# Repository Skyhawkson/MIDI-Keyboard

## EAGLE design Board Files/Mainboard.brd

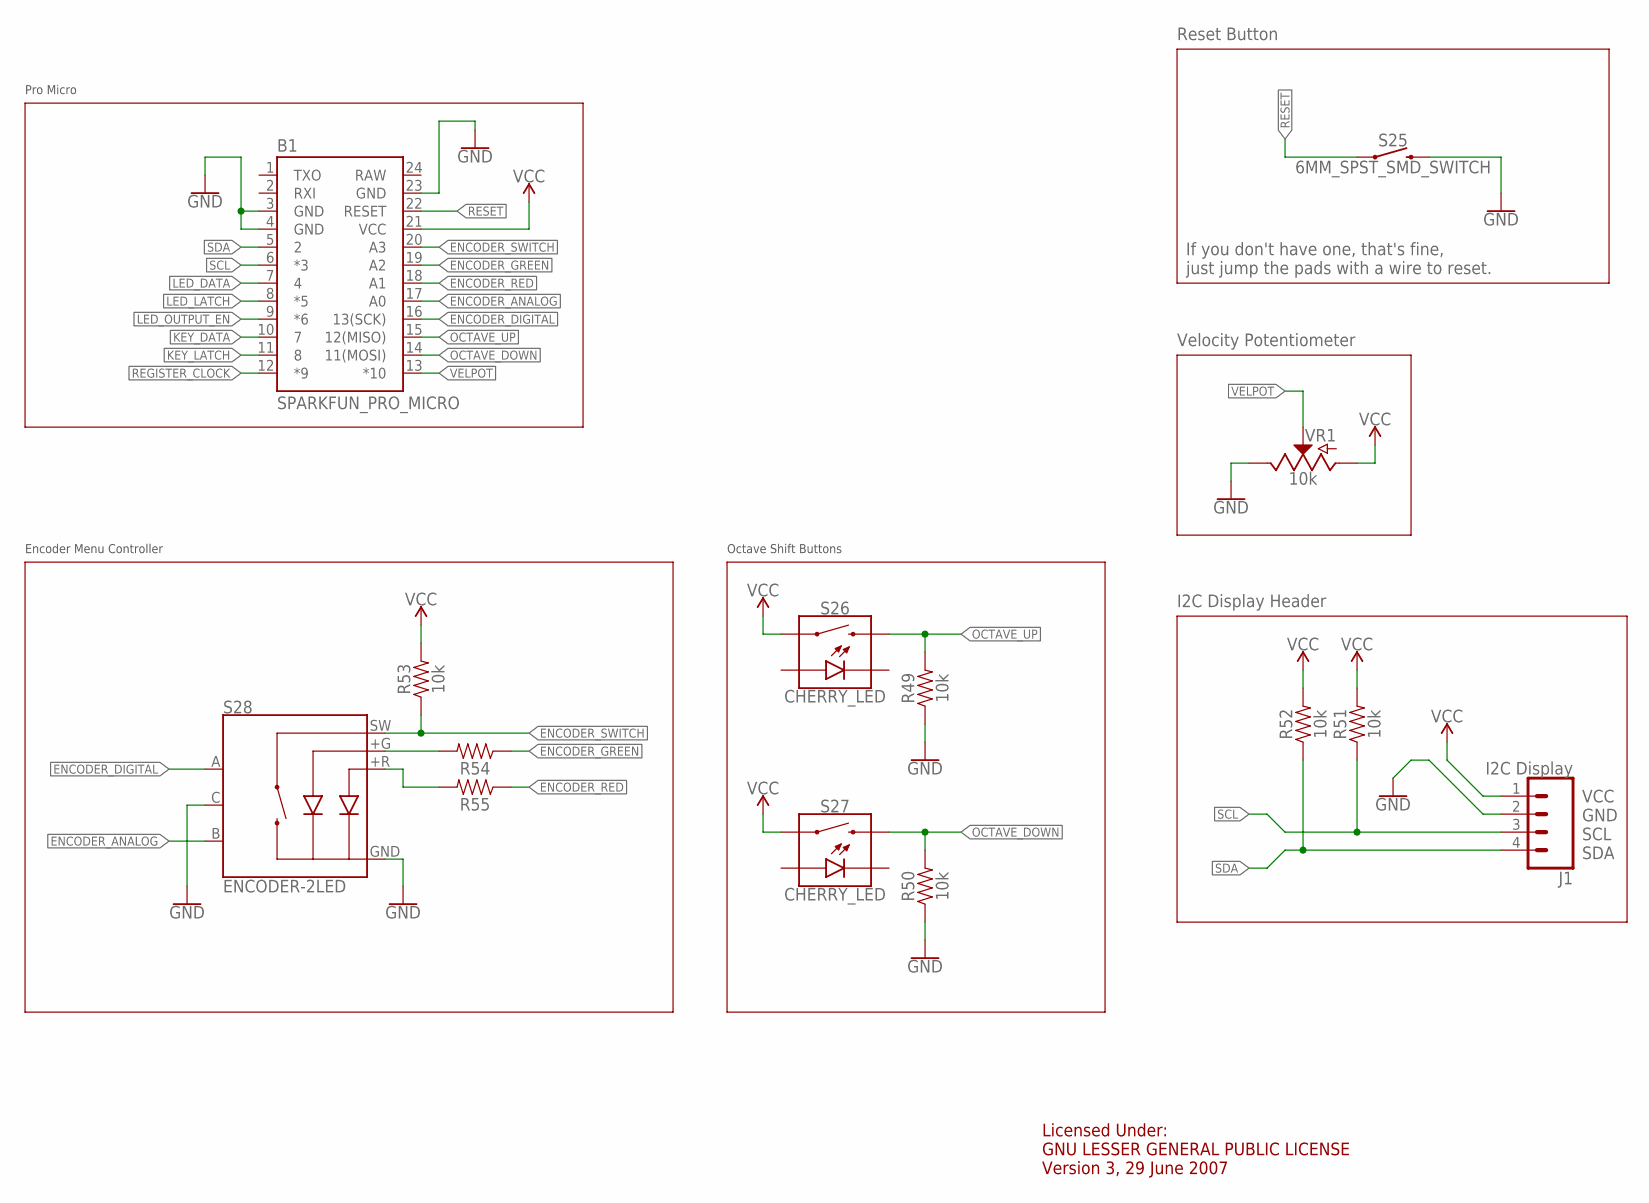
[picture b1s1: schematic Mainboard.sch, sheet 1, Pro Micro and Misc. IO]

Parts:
B1: SPARKFUN_PRO_MICRO
J1: I2C Display; 1X04
R49, R50, R51, R52, R53: 10k; AXIAL-0.3
R54, R55: AXIAL-0.3
S25: 6MM_SPST_SMD_SWITCH; TACTILE_SWITCH_SMD_6.0X3.5MM
S26, S27: CHERRY_LED; CHERRY-MX-LED
S28: ENCODER-2LED; ENCODER_LED_2
VR1: 10k; POT-PTH-ALPS

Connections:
ENCODER_ANALOG: B1.17 (A0), S28.B
ENCODER_DIGITAL: B1.16 (13(SCK)), S28.A
ENCODER_GREEN: B1.19 (A2), R54.P$1 (1)
ENCODER_RED: B1.18 (A1), R55.P$1 (1)
ENCODER_SWITCH: B1.20 (A3), R53.P$1 (1), S28.SW
GND: B1.3 (GND), B1.4 (GND), B1.23 (GND), J1.2, R49.P$1 (1), R50.P$1 (1), S25.2, S28.C, S28.GND (-), VR1.P$1 (E); also elsewhere on the board
KEY_DATA: B1.10 (7); also elsewhere on the board
KEY_LATCH: B1.11 (8); also elsewhere on the board
LED_DATA: B1.7 (4); also elsewhere on the board
LED_LATCH: B1.8 (*5); also elsewhere on the board
LED_OUTPUT_EN: B1.9 (*6); also elsewhere on the board
unnamed: R54.P$2 (2), S28.+G
unnamed: R55.P$2 (2), S28.+R
OCTAVE_DOWN: B1.14 (11(MOSI)), R50.P$2 (2), S27.S2 (2)
OCTAVE_UP: B1.15 (12(MISO)), R49.P$2 (2), S26.S2 (2)
RAW: B1.24 (RAW)
REGISTER_CLOCK: B1.12 (*9); also elsewhere on the board
RESET: B1.22 (RESET), S25.1
SCL: B1.6 (*3), J1.3, R51.P$1 (1)
SDA: B1.5 (2), J1.4, R52.P$1 (1)
VCC: B1.21 (VCC), J1.1, R51.P$2 (2), R52.P$2 (2), R53.P$2 (2), S26.S1 (1), S27.S1 (1), VR1.P$3 (A); also elsewhere on the board
VELPOT: B1.13 (*10), VR1.P$2 (S)

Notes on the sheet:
Reset Button
Velocity Potentiometer
VCC GND SCL SDA
I2C Display Header
If you don't have one, that's fine, just jump the pads with a wire to reset.
Licensed Under: GNU LESSER GENERAL PUBLIC LICENSE Version 3, 29 June 2007
Octave Shift Buttons
Encoder Menu Controller
Pro Micro

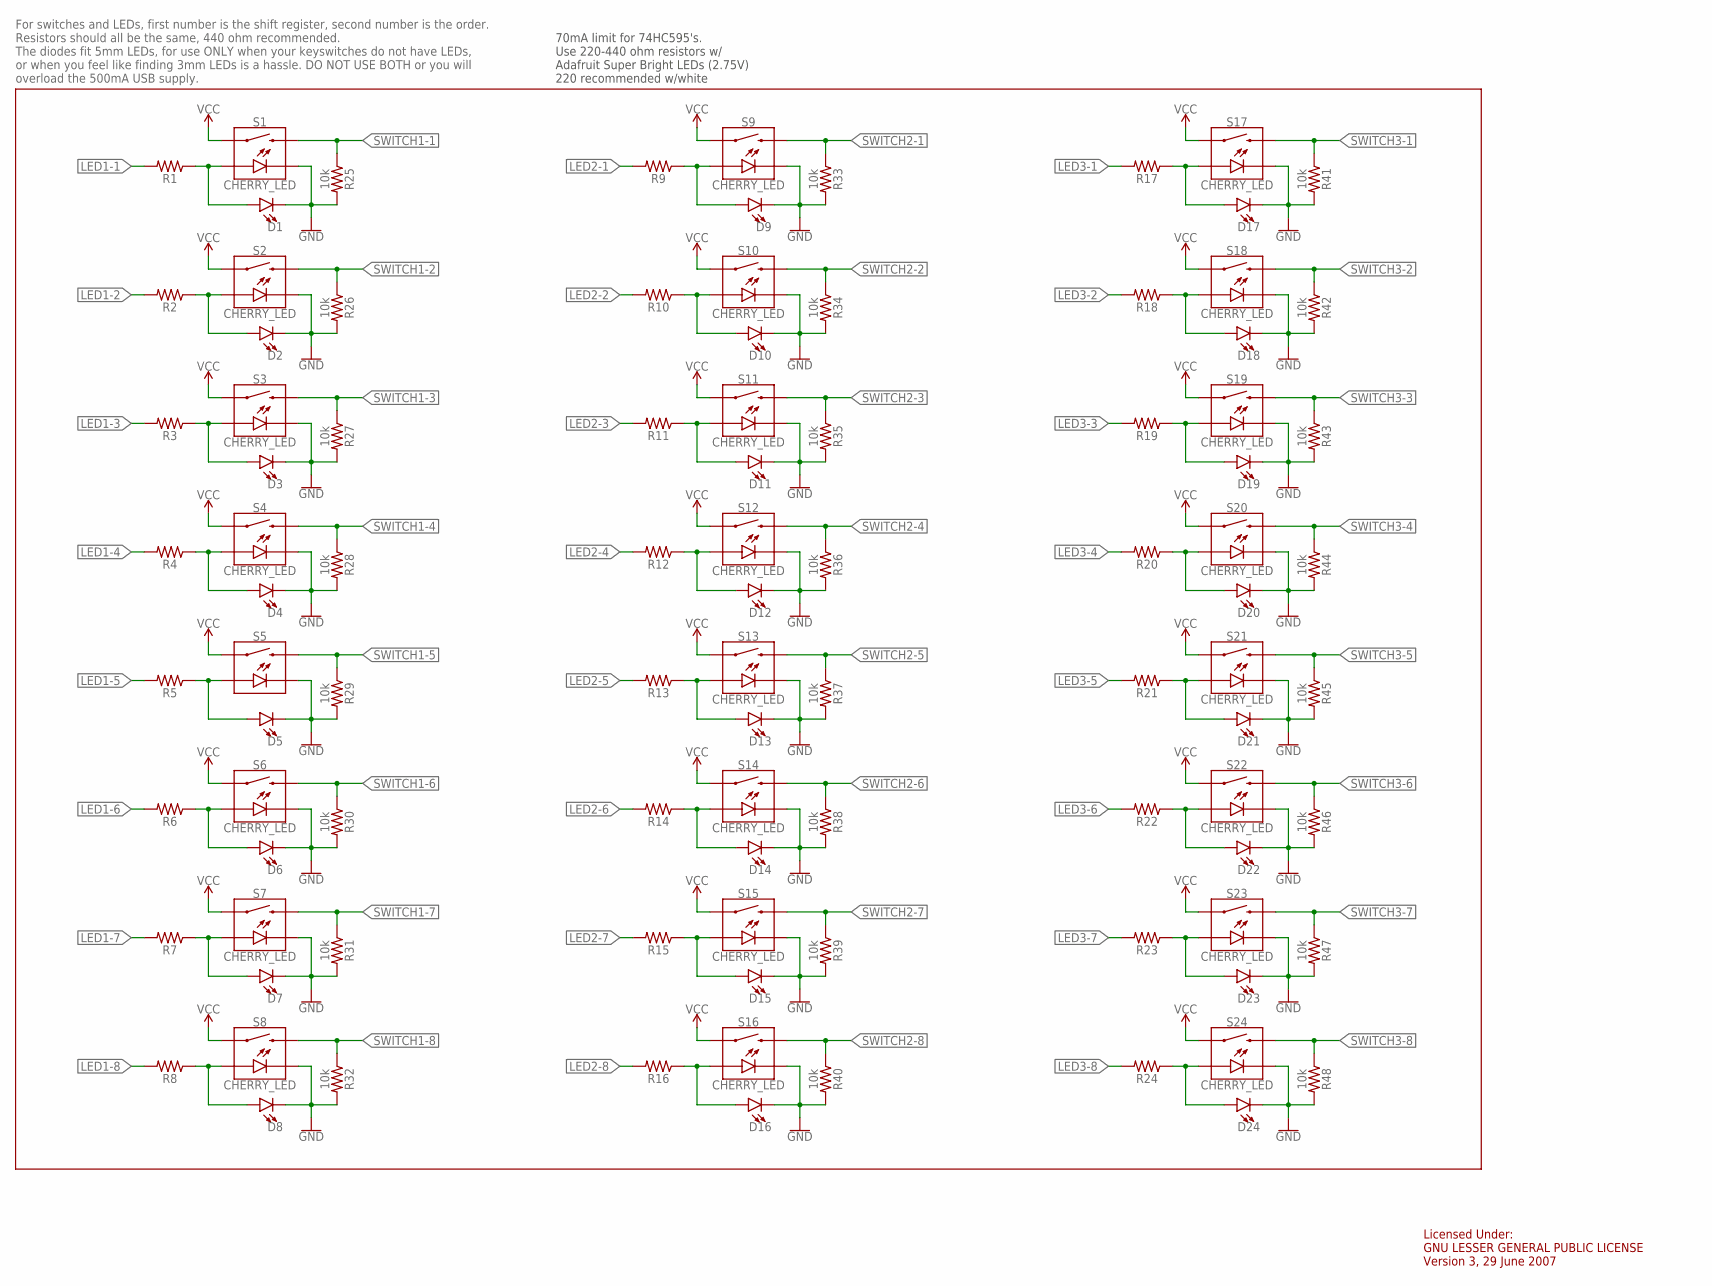
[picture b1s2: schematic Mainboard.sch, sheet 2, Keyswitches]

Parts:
D1, D2, D3, D4, D5, D6, D7, D8, D9, D10, D11, D12, D13, D14, D15, D16, D17, D18, D19, D20, D21, D22, D23, D24: LED5MM; LED_5MM
R1, R2, R3, R4, R5, R6, R7, R8, R9, R10, R11, R12, R13, R14, R15, R16, R17, R18, R19, R20, R21, R22, R23, R24: AXIAL-0.3
R25, R26, R27, R28, R29, R30, R31, R32, R33, R34, R35, R36, R37, R38, R39, R40, R41, R42, R43, R44, R45, R46, R47, R48: 10k; AXIAL-0.3
S1, S2, S3, S4, S6, S7, S8, S9, S10, S11, S12, S13, S14, S15, S16, S17, S18, S19, S20, S21, S22, S23, S24: CHERRY_LED; CHERRY-MX-LED
S5: MOMENTARY-SWITCH-SPST-LED-PTH-CHERRY; CHERRY-MX-LED

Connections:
GND: D1.K (C), D2.K (C), D3.K (C), D4.K (C), D5.K (C), D6.K (C), D7.K (C), D8.K (C), D9.K (C), D10.K (C), D11.K (C), D12.K (C), D13.K (C), D14.K (C), D15.K (C), D16.K (C), D17.K (C), D18.K (C), D19.K (C), D20.K (C), D21.K (C), D22.K (C), D23.K (C), D24.K (C), R25.P$2 (2), R26.P$2 (2), R27.P$2 (2), R28.P$2 (2), R29.P$2 (2), R30.P$2 (2), R31.P$2 (2), R32.P$2 (2), R33.P$2 (2), R34.P$2 (2), R35.P$2 (2), R36.P$2 (2), R37.P$2 (2), R38.P$2 (2), R39.P$2 (2), R40.P$2 (2), R41.P$2 (2), R42.P$2 (2), R43.P$2 (2), R44.P$2 (2), R45.P$2 (2), R46.P$2 (2), R47.P$2 (2), R48.P$2 (2), S1.K (C), S2.K (C), S3.K (C), S4.K (C), S5.K (C), S6.K (C), S7.K (C), S8.K (C), S9.K (C), S10.K (C), S11.K (C), S12.K (C), S13.K (C), S14.K (C), S15.K (C), S16.K (C), S17.K (C), S18.K (C), S19.K (C), S20.K (C), S21.K (C), S22.K (C), S23.K (C), S24.K (C); also elsewhere on the board
LED1-1: R1.P$2 (2); also elsewhere on the board
LED1-2: R2.P$2 (2); also elsewhere on the board
LED1-3: R3.P$2 (2); also elsewhere on the board
LED1-4: R4.P$2 (2); also elsewhere on the board
LED1-5: R5.P$2 (2); also elsewhere on the board
LED1-6: R6.P$2 (2); also elsewhere on the board
LED1-7: R7.P$2 (2); also elsewhere on the board
LED1-8: R8.P$2 (2); also elsewhere on the board
LED2-1: R9.P$2 (2); also elsewhere on the board
LED2-2: R10.P$2 (2); also elsewhere on the board
LED2-3: R11.P$2 (2); also elsewhere on the board
LED2-4: R12.P$2 (2); also elsewhere on the board
LED2-5: R13.P$2 (2); also elsewhere on the board
LED2-6: R14.P$2 (2); also elsewhere on the board
LED2-7: R15.P$2 (2); also elsewhere on the board
LED2-8: R16.P$2 (2); also elsewhere on the board
LED3-1: R17.P$2 (2); also elsewhere on the board
LED3-2: R18.P$2 (2); also elsewhere on the board
LED3-3: R19.P$2 (2); also elsewhere on the board
LED3-4: R20.P$2 (2); also elsewhere on the board
LED3-5: R21.P$2 (2); also elsewhere on the board
LED3-6: R22.P$2 (2); also elsewhere on the board
LED3-7: R23.P$2 (2); also elsewhere on the board
LED3-8: R24.P$2 (2); also elsewhere on the board
unnamed: D1.A, R1.P$1 (1), S1.A
unnamed: D2.A, R2.P$1 (1), S2.A
unnamed: D3.A, R3.P$1 (1), S3.A
unnamed: D4.A, R4.P$1 (1), S4.A
unnamed: D5.A, R5.P$1 (1), S5.A
unnamed: D6.A, R6.P$1 (1), S6.A
unnamed: D7.A, R7.P$1 (1), S7.A
unnamed: D8.A, R8.P$1 (1), S8.A
unnamed: D9.A, R9.P$1 (1), S9.A
unnamed: D10.A, R10.P$1 (1), S10.A
unnamed: D11.A, R11.P$1 (1), S11.A
unnamed: D12.A, R12.P$1 (1), S12.A
unnamed: D13.A, R13.P$1 (1), S13.A
unnamed: D14.A, R14.P$1 (1), S14.A
unnamed: D15.A, R15.P$1 (1), S15.A
unnamed: D16.A, R16.P$1 (1), S16.A
unnamed: D17.A, R17.P$1 (1), S17.A
unnamed: D18.A, R18.P$1 (1), S18.A
unnamed: D19.A, R19.P$1 (1), S19.A
unnamed: D20.A, R20.P$1 (1), S20.A
unnamed: D21.A, R21.P$1 (1), S21.A
unnamed: D22.A, R22.P$1 (1), S22.A
unnamed: D23.A, R23.P$1 (1), S23.A
unnamed: D24.A, R24.P$1 (1), S24.A
SWITCH1-1: R25.P$1 (1), S1.S2 (2); also elsewhere on the board
SWITCH1-2: R26.P$1 (1), S2.S2 (2); also elsewhere on the board
SWITCH1-3: R27.P$1 (1), S3.S2 (2); also elsewhere on the board
SWITCH1-4: R28.P$1 (1), S4.S2 (2); also elsewhere on the board
SWITCH1-5: R29.P$1 (1), S5.S2 (2); also elsewhere on the board
SWITCH1-6: R30.P$1 (1), S6.S2 (2); also elsewhere on the board
SWITCH1-7: R31.P$1 (1), S7.S2 (2); also elsewhere on the board
SWITCH1-8: R32.P$1 (1), S8.S2 (2); also elsewhere on the board
SWITCH2-1: R33.P$1 (1), S9.S2 (2); also elsewhere on the board
SWITCH2-2: R34.P$1 (1), S10.S2 (2); also elsewhere on the board
SWITCH2-3: R35.P$1 (1), S11.S2 (2); also elsewhere on the board
SWITCH2-4: R36.P$1 (1), S12.S2 (2); also elsewhere on the board
SWITCH2-5: R37.P$1 (1), S13.S2 (2); also elsewhere on the board
SWITCH2-6: R38.P$1 (1), S14.S2 (2); also elsewhere on the board
SWITCH2-7: R39.P$1 (1), S15.S2 (2); also elsewhere on the board
SWITCH2-8: R40.P$1 (1), S16.S2 (2); also elsewhere on the board
SWITCH3-1: R41.P$1 (1), S17.S2 (2); also elsewhere on the board
SWITCH3-2: R42.P$1 (1), S18.S2 (2); also elsewhere on the board
SWITCH3-3: R43.P$1 (1), S19.S2 (2); also elsewhere on the board
SWITCH3-4: R44.P$1 (1), S20.S2 (2); also elsewhere on the board
SWITCH3-5: R45.P$1 (1), S21.S2 (2); also elsewhere on the board
SWITCH3-6: R46.P$1 (1), S22.S2 (2); also elsewhere on the board
SWITCH3-7: R47.P$1 (1), S23.S2 (2); also elsewhere on the board
SWITCH3-8: R48.P$1 (1), S24.S2 (2); also elsewhere on the board
VCC: S1.S1 (1), S2.S1 (1), S3.S1 (1), S4.S1 (1), S5.S1 (1), S6.S1 (1), S7.S1 (1), S8.S1 (1), S9.S1 (1), S10.S1 (1), S11.S1 (1), S12.S1 (1), S13.S1 (1), S14.S1 (1), S15.S1 (1), S16.S1 (1), S17.S1 (1), S18.S1 (1), S19.S1 (1), S20.S1 (1), S21.S1 (1), S22.S1 (1), S23.S1 (1), S24.S1 (1); also elsewhere on the board

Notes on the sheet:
For switches and LEDs, first number is the shift register, second number is the order. Resistors should all be the same, 440 ohm recommended. The diodes fit 5mm LEDs, for use ONLY when your keyswitches do not have LEDs, or when you feel like finding 3mm LEDs is a hassle. DO NOT USE BOTH or you will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
70mA limit for 74HC595's. Use 220-440 ohm resistors w/ Adafruit Super Bright LEDs (2.75V) 220 recommended w/white
Licensed Under: GNU LESSER GENERAL PUBLIC LICENSE Version 3, 29 June 2007

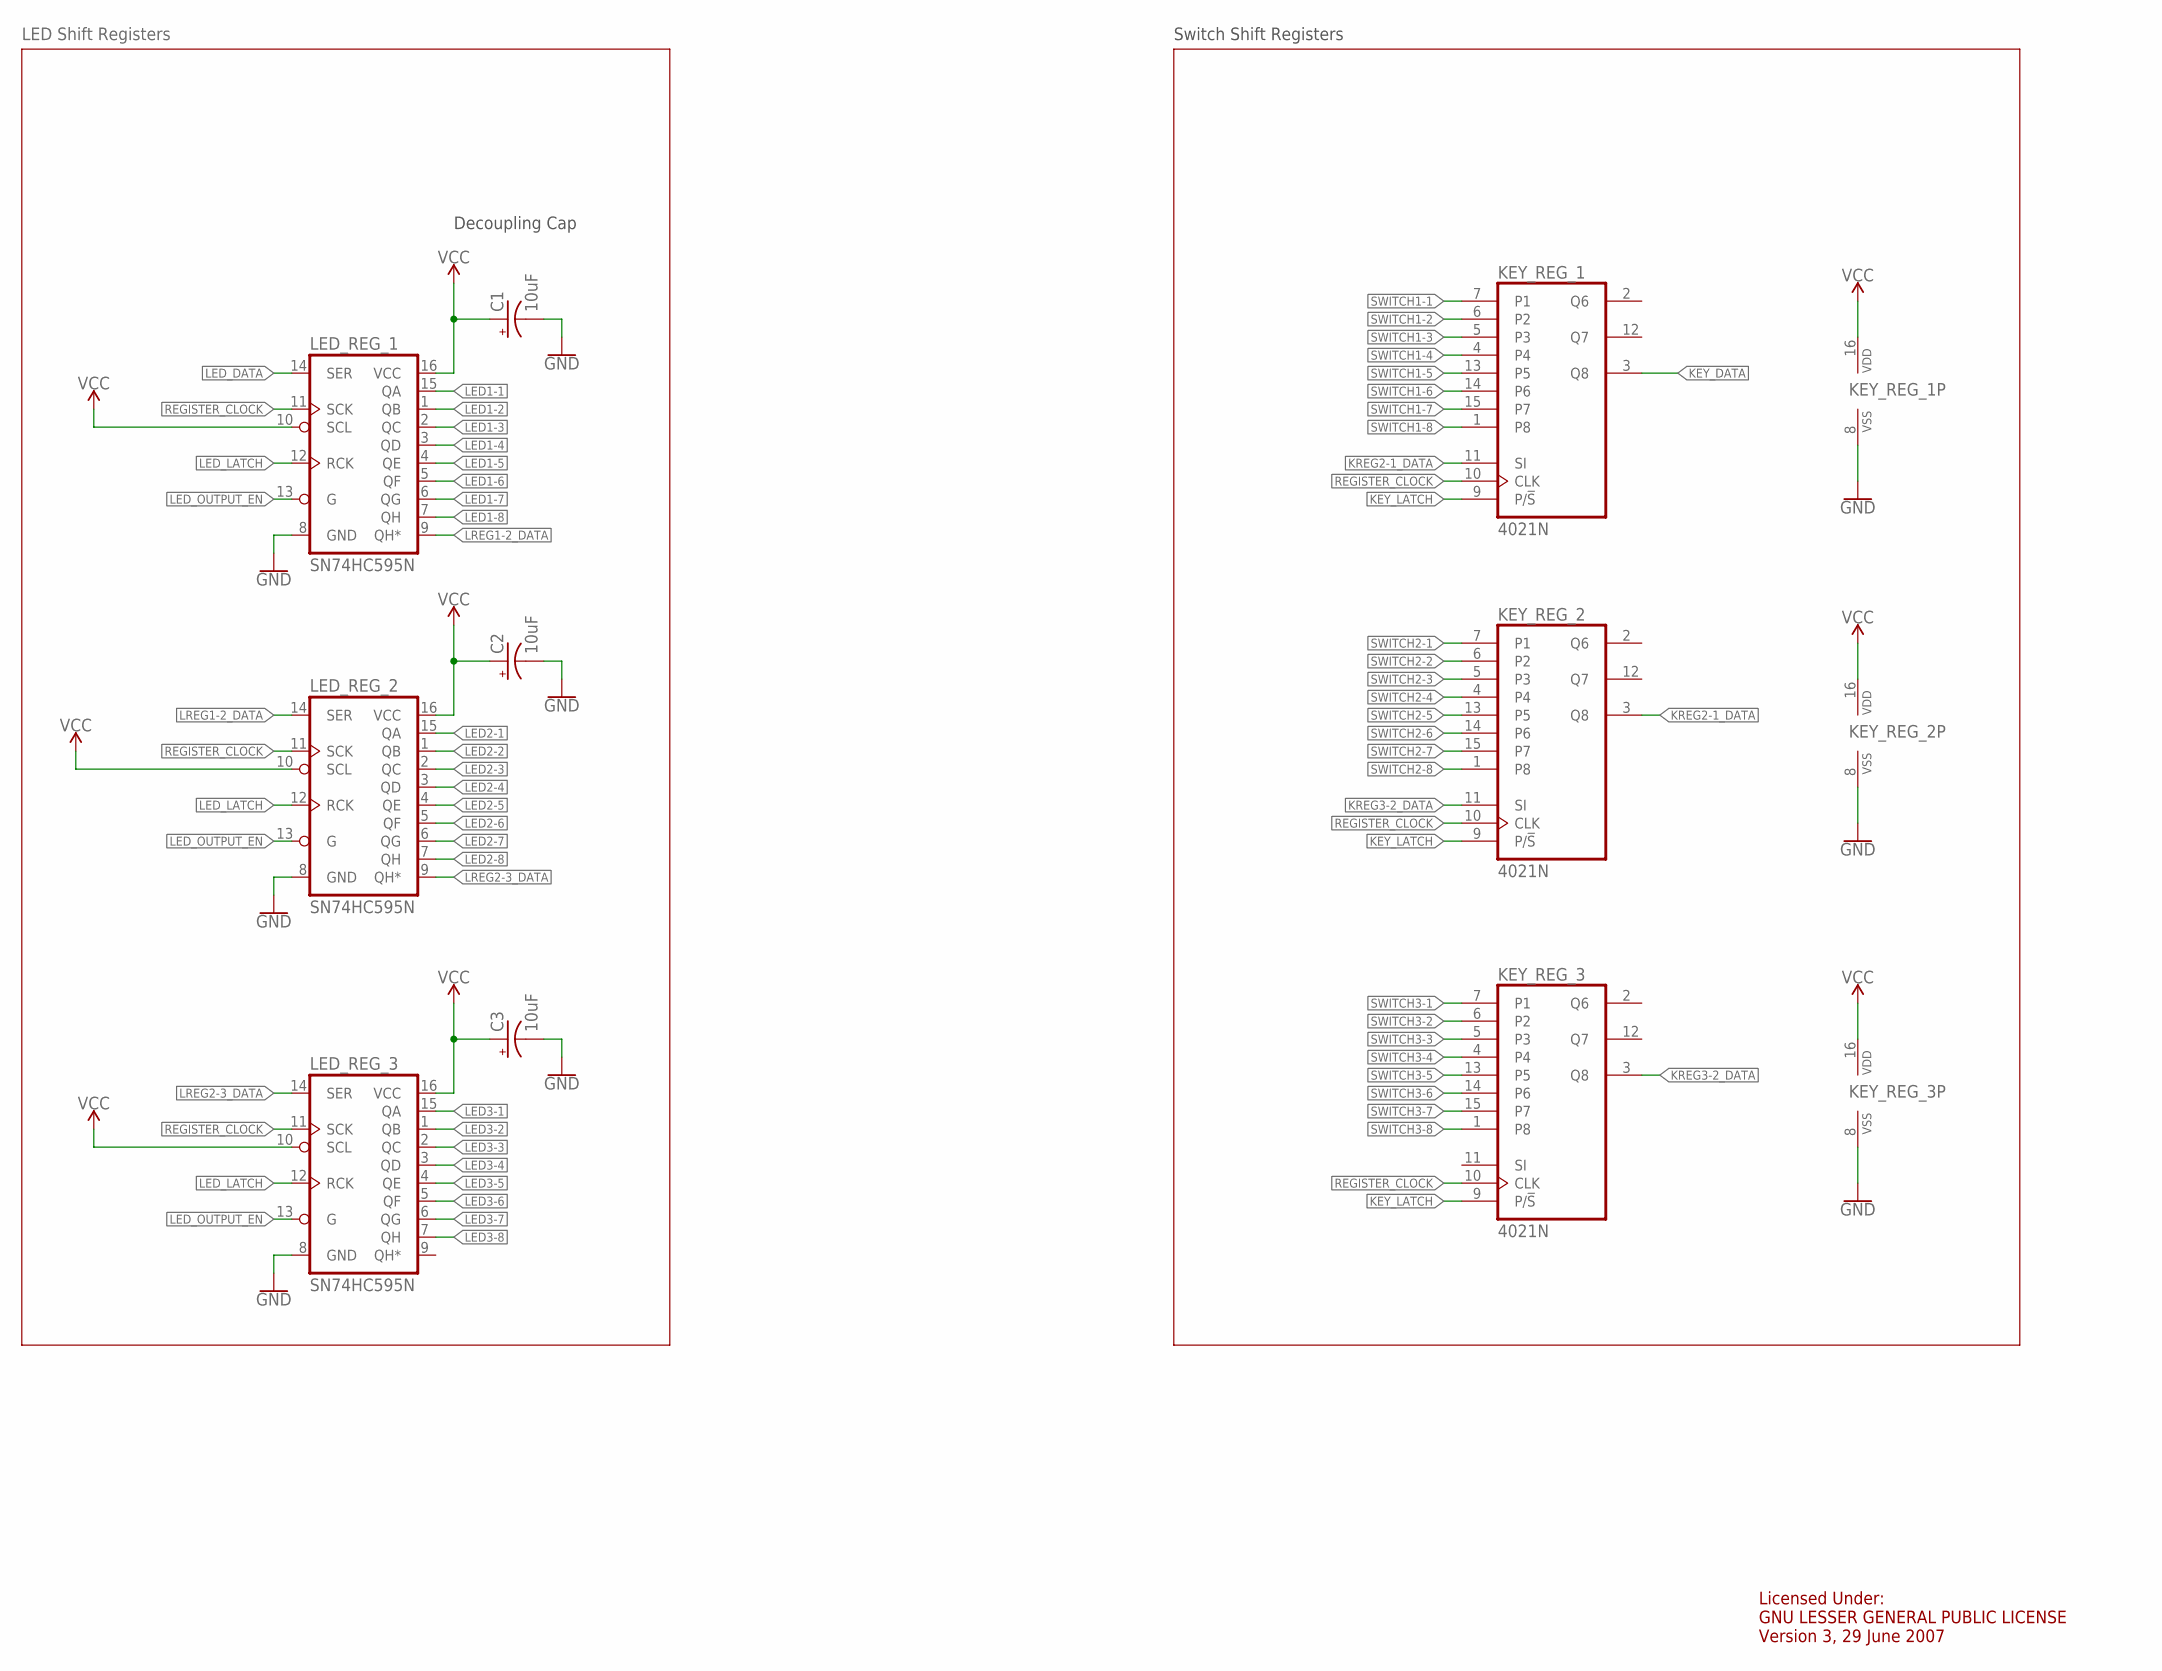
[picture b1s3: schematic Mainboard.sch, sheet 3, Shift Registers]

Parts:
C1, C2, C3: 10uF; CPOL-RADIAL-2.5MM-5MM
KEY_REG_1, KEY_REG_2, KEY_REG_3: 4021N; DIL16
LED_REG_1, LED_REG_2, LED_REG_3: SN74HC595N; DIP16

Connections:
GND: C1.2 (-), C2.2 (-), C3.2 (-), KEY_REG_1.8 (VSS), KEY_REG_2.8 (VSS), KEY_REG_3.8 (VSS), LED_REG_1.8 (GND), LED_REG_2.8 (GND), LED_REG_3.8 (GND); also elsewhere on the board
KEY_DATA: KEY_REG_1.3 (Q8); also elsewhere on the board
KEY_LATCH: KEY_REG_1.9 (P/!S), KEY_REG_2.9 (P/!S), KEY_REG_3.9 (P/!S); also elsewhere on the board
KREG2-1_DATA: KEY_REG_1.11 (SI), KEY_REG_2.3 (Q8)
KREG3-2_DATA: KEY_REG_2.11 (SI), KEY_REG_3.3 (Q8)
LED1-1: LED_REG_1.15 (QA); also elsewhere on the board
LED1-2: LED_REG_1.1 (QB); also elsewhere on the board
LED1-3: LED_REG_1.2 (QC); also elsewhere on the board
LED1-4: LED_REG_1.3 (QD); also elsewhere on the board
LED1-5: LED_REG_1.4 (QE); also elsewhere on the board
LED1-6: LED_REG_1.5 (QF); also elsewhere on the board
LED1-7: LED_REG_1.6 (QG); also elsewhere on the board
LED1-8: LED_REG_1.7 (QH); also elsewhere on the board
LED2-1: LED_REG_2.15 (QA); also elsewhere on the board
LED2-2: LED_REG_2.1 (QB); also elsewhere on the board
LED2-3: LED_REG_2.2 (QC); also elsewhere on the board
LED2-4: LED_REG_2.3 (QD); also elsewhere on the board
LED2-5: LED_REG_2.4 (QE); also elsewhere on the board
LED2-6: LED_REG_2.5 (QF); also elsewhere on the board
LED2-7: LED_REG_2.6 (QG); also elsewhere on the board
LED2-8: LED_REG_2.7 (QH); also elsewhere on the board
LED3-1: LED_REG_3.15 (QA); also elsewhere on the board
LED3-2: LED_REG_3.1 (QB); also elsewhere on the board
LED3-3: LED_REG_3.2 (QC); also elsewhere on the board
LED3-4: LED_REG_3.3 (QD); also elsewhere on the board
LED3-5: LED_REG_3.4 (QE); also elsewhere on the board
LED3-6: LED_REG_3.5 (QF); also elsewhere on the board
LED3-7: LED_REG_3.6 (QG); also elsewhere on the board
LED3-8: LED_REG_3.7 (QH); also elsewhere on the board
LED_DATA: LED_REG_1.14 (SER); also elsewhere on the board
LED_LATCH: LED_REG_1.12 (RCK), LED_REG_2.12 (RCK), LED_REG_3.12 (RCK); also elsewhere on the board
LED_OUTPUT_EN: LED_REG_1.13 (G), LED_REG_2.13 (G), LED_REG_3.13 (G); also elsewhere on the board
LREG1-2_DATA: LED_REG_1.9 (QH*), LED_REG_2.14 (SER)
LREG2-3_DATA: LED_REG_2.9 (QH*), LED_REG_3.14 (SER)
REGISTER_CLOCK: KEY_REG_1.10 (CLK), KEY_REG_2.10 (CLK), KEY_REG_3.10 (CLK), LED_REG_1.11 (SCK), LED_REG_2.11 (SCK), LED_REG_3.11 (SCK); also elsewhere on the board
SWITCH1-1: KEY_REG_1.7 (P1); also elsewhere on the board
SWITCH1-2: KEY_REG_1.6 (P2); also elsewhere on the board
SWITCH1-3: KEY_REG_1.5 (P3); also elsewhere on the board
SWITCH1-4: KEY_REG_1.4; also elsewhere on the board
SWITCH1-5: KEY_REG_1.13 (P5); also elsewhere on the board
SWITCH1-6: KEY_REG_1.14 (P6); also elsewhere on the board
SWITCH1-7: KEY_REG_1.15 (P7); also elsewhere on the board
SWITCH1-8: KEY_REG_1.1 (P8); also elsewhere on the board
SWITCH2-1: KEY_REG_2.7 (P1); also elsewhere on the board
SWITCH2-2: KEY_REG_2.6 (P2); also elsewhere on the board
SWITCH2-3: KEY_REG_2.5 (P3); also elsewhere on the board
SWITCH2-4: KEY_REG_2.4; also elsewhere on the board
SWITCH2-5: KEY_REG_2.13 (P5); also elsewhere on the board
SWITCH2-6: KEY_REG_2.14 (P6); also elsewhere on the board
SWITCH2-7: KEY_REG_2.15 (P7); also elsewhere on the board
SWITCH2-8: KEY_REG_2.1 (P8); also elsewhere on the board
SWITCH3-1: KEY_REG_3.7 (P1); also elsewhere on the board
SWITCH3-2: KEY_REG_3.6 (P2); also elsewhere on the board
SWITCH3-3: KEY_REG_3.5 (P3); also elsewhere on the board
SWITCH3-4: KEY_REG_3.4; also elsewhere on the board
SWITCH3-5: KEY_REG_3.13 (P5); also elsewhere on the board
SWITCH3-6: KEY_REG_3.14 (P6); also elsewhere on the board
SWITCH3-7: KEY_REG_3.15 (P7); also elsewhere on the board
SWITCH3-8: KEY_REG_3.1 (P8); also elsewhere on the board
VCC: C1.1 (+), C2.1 (+), C3.1 (+), KEY_REG_1.16 (VDD), KEY_REG_2.16 (VDD), KEY_REG_3.16 (VDD), LED_REG_1.10 (SCL), LED_REG_1.16 (VCC), LED_REG_2.10 (SCL), LED_REG_2.16 (VCC), LED_REG_3.10 (SCL), LED_REG_3.16 (VCC); also elsewhere on the board

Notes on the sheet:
Decoupling Cap
LED Shift Registers
Switch Shift Registers
Licensed Under: GNU LESSER GENERAL PUBLIC LICENSE Version 3, 29 June 2007

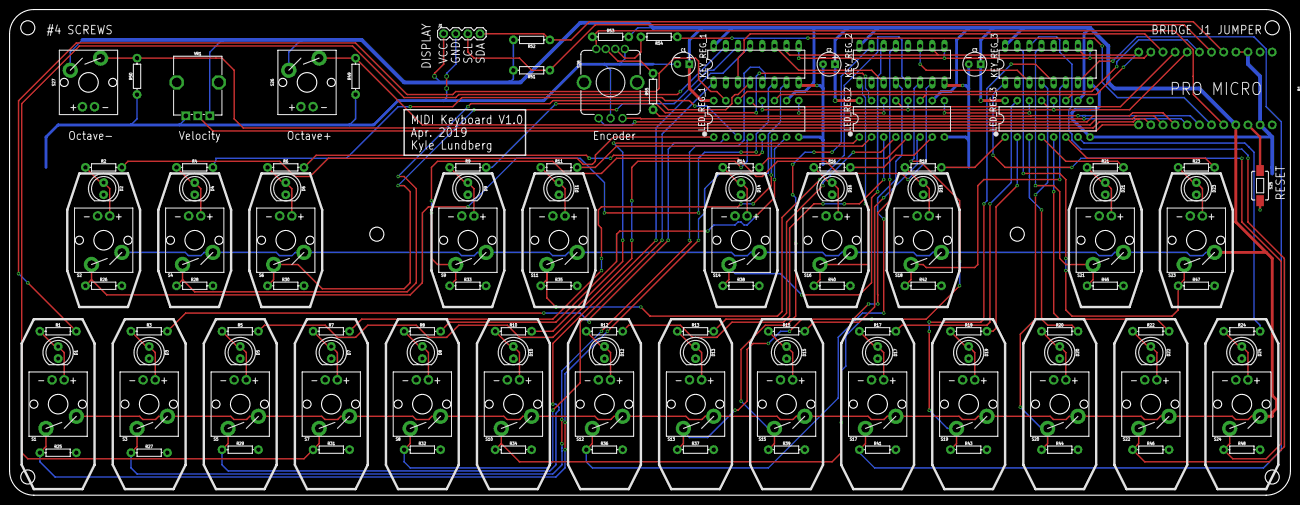
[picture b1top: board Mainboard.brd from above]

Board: 2 copper layers, 268.0 x 101.6 mm, 119 parts (0 on the bottom side), 97 nets.

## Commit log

2019-04-01 Added libraries
    Added Cherry MX and Pro Micro Footprint libraries
2019-04-01 First Eagle Files
    Added Cherry switches, 5MM LEDs, and resistors to schematic.
2019-04-01 Switched to Sparkfun libraries
    Removed pro micro footprint in lieu of official sparkfun footprint. Added in the LED-controlling shift registers.
2019-04-02 Added .gitignore
    See title -_-
2019-04-03 Board Updates
    -Reset Switch
    -Velocity Pot
    -Frames
    -Started connecting shift registers
2019-04-04 Finished Shift Registers
    -Finished pins on 595s
    -Added and completed pins on 4021B's
    -Added 10k resistors to switch side
    -Added issues to test and consider to github
2019-04-04 Completed First Schematic Draft
    -Switched to Sparkfun Cherry parts
    -Added illuminated rotary encoder
    -Connected all microcontroller pins
    -Finished shift register pins
    -Added octave shift buttons
2019-04-04 Beginning Board Work
    Tentative board dimensions and layout
2019-04-05 Board Layout Update
    -Routed VCC and GND to white keys
    -Routed GND to black keys
    -Placed most components on board
2019-04-05 Preliminary Keycap CAD
    -Modeled a test flat white key cap
    -Added references used to create stem socket dimensions
2019-04-07 Added Key .STL files
    -Added white and black key .STLs
    -Consolidated Arduino folder
2019-04-07 Routed LEDs and most switches
    -Routed all LEDs
    -Routes 2/3rds of switches
    -Probably need to reroute the right side
2019-04-08 Board Updates, Keycap Updates, Trimmed Libraries
    -Finished routing switch and LED traces, will need cleanup
    -Made dished versions of keycaps. Thickened top and bottom walls of key stems
    -Removed extraneous cherry libraries; fully using Sparkfun and native Eagle ones now
2019-04-10 Began New PCB
    -Deleted cramped PCB, started new layout.
2019-04-14 Updated BRD and SCH
    -Added more smoothing caps to schematic, placed things, reverted to old STL files
2019-04-14 Finished Manual Routing
    Finished routing manual traces. Will autoroute the switch and LED traces
2019-04-15 Preliminary Finished Layout
    WIth help of autorouter and hand finishing, completed an initial PCB layout
2019-04-15 Added Dial .STLs and Proven Key STLs
    -Added Octave Keys
    -Added Encoder Dial
    -Added Velocity Dial
    -Uploaded old, proven white/black key .STLs
2019-04-17 Updated STLs and Removed Thermal Checking
    -Updated Encoder Dial to V1.1
    -Updated Velocity Dial to V1.1
    -Changed diameter from 6.25mm to 6.125mm on both
    -Removed thermal checks on board DRC
2019-04-17 Further Trimmed Dial Diameter
    -Moved shaft diameter to nominal 6mm, since measured parts were ~5.95mm stem diameter
2019-04-17 Cleaned up more routing
    -Still need to do physical layout check
2019-04-18 Finished Mainboard V1.0
    -Added holes
    -Labeled everything
    -Final trace cleanup
2019-04-18 Casing Completed. Except Screen
    -Completed base housing
    -Need to add OLED screen
2019-04-22 Added Top and Bottom Cover STLs
2019-04-22 Updated Parts and Assembly
2019-04-23 Updated Assembly and Board Tweaks
    -Added color to parts in assembly, made renders
    -Did final layout adjustments on mainboard. Renamed resistors
2019-04-23 Finished Mainboard and Assembly
    -Added mounting holes for display
    -Fixed Switch 19 being .05in out of place

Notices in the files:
parts and their libraries:
SparkFun-Boards: Licensing: Creative Commons ShareAlike 4.0 International - https://creativecommons.org/licenses/by-sa/4.0
